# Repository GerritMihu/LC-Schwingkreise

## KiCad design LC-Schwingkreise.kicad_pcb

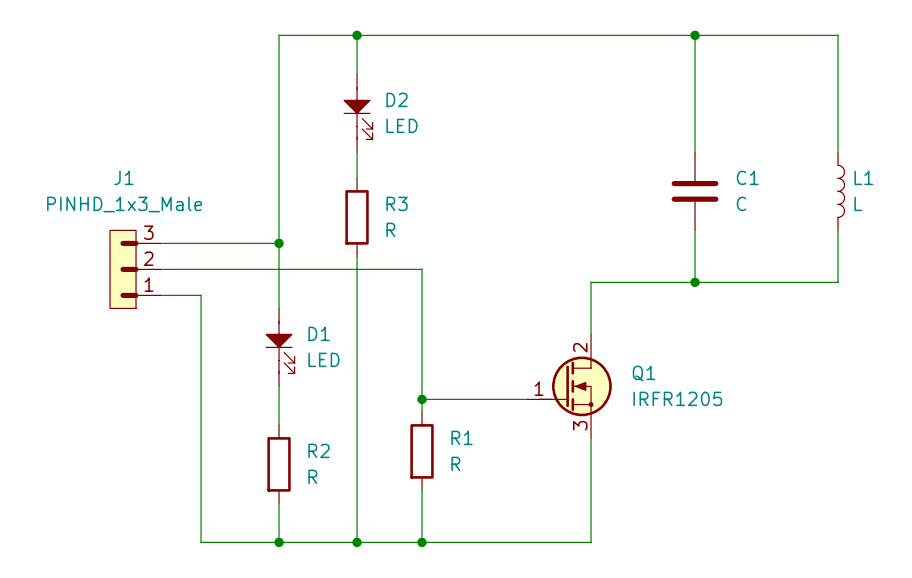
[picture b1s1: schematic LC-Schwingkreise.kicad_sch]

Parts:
C1: C; C_1206_3216Metric_Pad1.33x1.80mm_HandSolder
D1, D2: LED; LED_0402_1005Metric_Pad0.77x0.64mm_HandSolder
J1: PINHD_1x3_Male; PinHeader_1x03_P2.54mm_Vertical
L1: L; 40dia10turn
Q1: IRFR1205; TO-252-2
R1, R2, R3: R; R_1206_3216Metric_Pad1.30x1.75mm_HandSolder

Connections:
unnamed: C1.1, D1.2, D2.2, J1.3, L1.1
unnamed: D1.1, R2.1
unnamed: D2.1, R3.1
unnamed: C1.2, L1.2, Q1.2 (D)
unnamed: J1.2, Q1.1 (G), R1.1
unnamed: J1.1, Q1.3 (S), R1.2, R2.2, R3.2

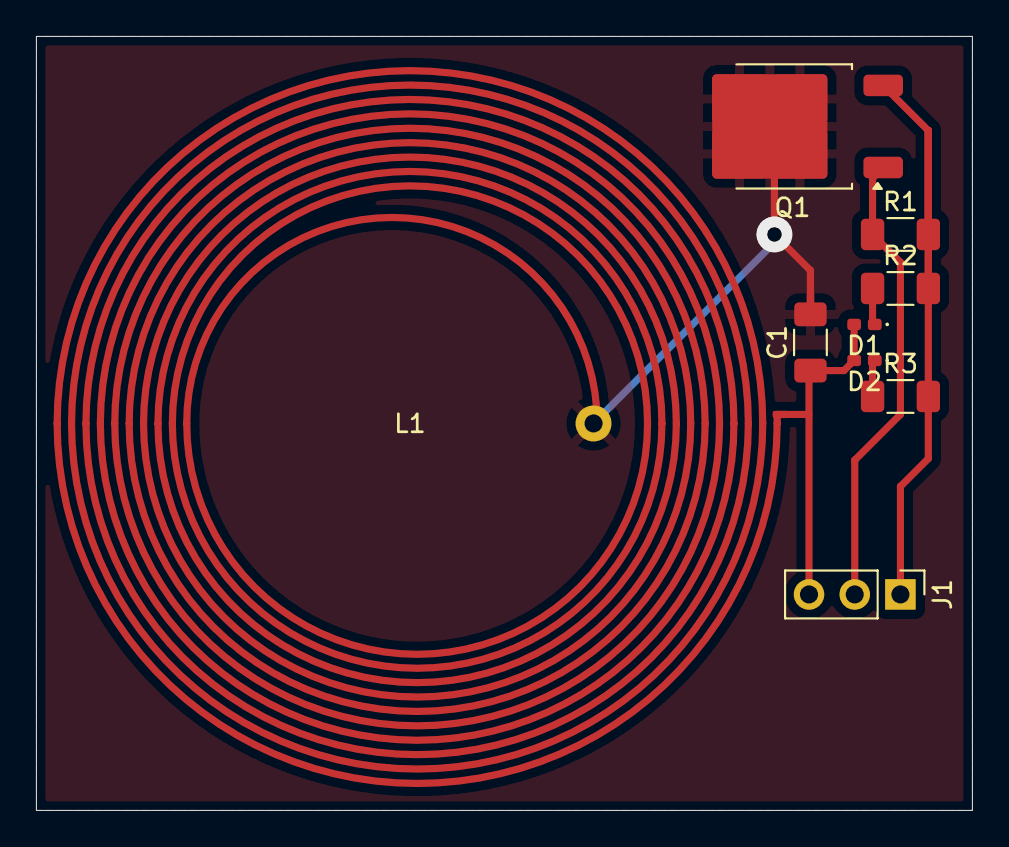
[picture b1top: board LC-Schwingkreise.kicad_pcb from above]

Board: 2 copper layers, 52.0 x 43.0 mm, 9 parts (0 on the bottom side), 6 nets.

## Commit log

2024-04-30 ready for prod
